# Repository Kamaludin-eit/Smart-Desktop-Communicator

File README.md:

### Smart Desktop Communicator – Design-Dokumentation

**Rev 1.0 | Kamaludin Ali**

\---

#### Übersicht

ESP32-S3-basiertes stationäres IP-Telefon mit PoE-Versorgung, Wired Ethernet,
I2S-Audio und OLED-Display. 4-lagige PCB (150 × 80 mm).

\---

#### Wichtigste Design-Entscheidungen

##### 1\. Mikrocontroller – ESP32-S3-WROOM-1

* Dual-Core LX7, 16 MB Flash, 8 MB PSRAM, 2.4 GHz WLAN integriert
* Natives USB Serial/JTAG auf GPIO19/20 – kein separater USB-UART-Chip nötig
* I2S-Peripheral für DAC (MAX98357A) und PDM-Mikrofon (IM69D120) separat nutzbar
* SPI-Peripheral für W5500 Ethernet-Controller

##### 2\. PoE-Versorgung – TPS2378DDA + PDQE30-Q48-S5-D

* TPS2378DDA: IEEE 802.3at Type-2 PD-Controller (bis 30 W)
* Kein integrierter DC/DC – externer isolierter Wandler PDQE30 (48 V → 5 V, 30 W)
* Isolation trennt PWR\_GND (48 V-Seite) vollständig von GNDD/GNDA (Systemseite)
* Alternativversorgung via USB-C (5 V) mit Schottky-Dioden-OR-Schaltung#

##### 3\. RJ45-Connector – ARJP11A-MASA-B-A-EMU2 (Abracon)

* Integrierte Magnetics, Center-Tap, eingebauter Brückengleichrichter
* PRW+ (Pin 9) / PRW− (Pin 10): rektifizierte PoE-Spannung direkt abgreifbar
* Kein externer Brückengleichrichter oder separates Magnetics-Modul nötig
* Integrierte Status-LEDs (Link/Activity)

##### 4\. Ethernet – W5500

* Hardware-TCP/IP-Stack – entlastet ESP32-S3 vollständig
* SPI-Interface (bis 80 MHz), geringer Softwareaufwand

##### 5\. Audio-Ausgabe – MAX98357A

* I2S DAC + Class-D 3 W Verstärker in einem IC
* BTL-Ausgang: keine DC-Koppelkondensatoren am Lautsprecher nötig
* PVDD über Ferritperle L3 (600 Ω @ 100 MHz, 1 A) von 5V-Rail entkoppelt
* 3.3V-Logiksignale vom ESP32 kompatibel (VIH\_min = 1.5 V)
* Lautsprecher extern im Gehäuse montiert (akustische Echo-Minimierung)

##### 6\. Audio-Eingang – IM69D120 (Infineon)

* MEMS-Mikrofon mit PDM-Ausgang, SNR 69 dB, AOP 120 dB SPL
* Nativ vom ESP32-S3 PDM-Peripheral unterstützt
* VDD über eigene Ferritperle L4 (600 Ω @ 100 MHz, 50 mA) von VCCA\_MIC
* Software-AEC (Acoustic Echo Cancellation) via ESP-ADF

##### 7\. Massekonzept – 2 getrennte GND-Domänen

|Domäne|Verbindung|Komponenten|
|-|-|-|
|GNDD|Solder Jumper Pin 2 |ESP32, W5500 digital, Tasten, LEDs|
|GNDA|Solder Jumper Pin 1|W5500 PHY, IM69D120, MAX98357A, Quarz|

##### 8\. 4-Lagen PCB-Aufbau (150 × 80 mm)

|Lage|Inhalt|
|-|-|
|Layer 1 (Top)|Bauteile + Signale + GNDA-Kupferfläche|
|Layer 2 (In1)|+3,3V  |
|Layer 3 (In2)|GNDD-Kupferfläche|
|Layer 4 (Bottom)|Signale + GNDA-Kupferfläche|

* Digitale GND-Pads auf Top-Layer über Vias mit GNDD (In1) verbunden
* Analoge Komponenten direkt auf GNDA-Fläche (Top-Layer)

##### 9\. Versorgungsschienen

|Schiene|Quelle|Verbraucher|
|-|-|-|
|+48V\_POE|PRW+ via SMAJ58A|TPS2378DDA VDD|
|+5V|PDQE30 Ausgang|MAX98357A, AMS1117|
|+3.3V (VCCD)|AMS1117-3.3|ESP32, W5500 digital, Tasten, LEDs|
|VCCA\_ETH|VCCD via FB\_ETH (600Ω)|W5500 VCCA|
|VCCA\_MIC|VCCD via FB\_MIC (600Ω)|IM69D120 VDD|

### 

##### 10\. ESD-Schutz

|Interface|Schutz|
|-|-|
|PoE 48V|SMAJ58A (unidirektional, 58V)|
|USB-C VBUS|SMAJ5.0A (unidirektional, 5V)|
|USB-C D+/D−|USBLC6-2P6 (Low-C, bidirektional)|
|Ethernet TX/RX|Magnetics-Isolation im ARJP11A|

### 

##### 11\. USB-C – Amphenol 12401610E4#2A

* CC1/CC2: je 5.1 kΩ nach GNDD (5V UFP-Erkennung, kein PD-Controller nötig)
* Schottky-Diode OR-ing mit PoE-Versorgung
* D+/D−: direkt an ESP32 GPIO19/GPIO20 (natives USB JTAG/Serial)

##### 12\. HMI

* SSD1306 OLED 0.96" (128×64, I2C): Anrufstatus, IP, Uhrzeit
* 5 Taster: Annehmen/Auflegen, Vol+, Vol−, Stummschalten, Notruf
* 1 Status-LEDs:  Power(rot)
* Hardware-Entprellung: RC-Glied (100 kΩ + 1 µF) pro Taster

\---

#### Geplante Firmware-Architektur

* **ESP-IDF** v5.x + **ESP-ADF** (Audio Development Framework)
* SIP-Stack: sikorapatryk/sip-call oder OLIMEX/sip\_phone\_example als Referenz
* Codec: G.711 µ-law (PCMU, Payload Type 0)
* AEC: ESP-ADF eingebaut
* W5500-Treiber: arduino-ethernet oder esp-idf-w5500

\---

#### Wählscheibe

Nicht vorgesehen – Anrufsteuerung erfolgt über SIP-Server/PBX-Integration (z.B. FreePBX, Asterisk).

\---

## Revision History

|Rev|Datum|Änderung|
|-|-|-|
|1.0|2026-05|Erstversion|

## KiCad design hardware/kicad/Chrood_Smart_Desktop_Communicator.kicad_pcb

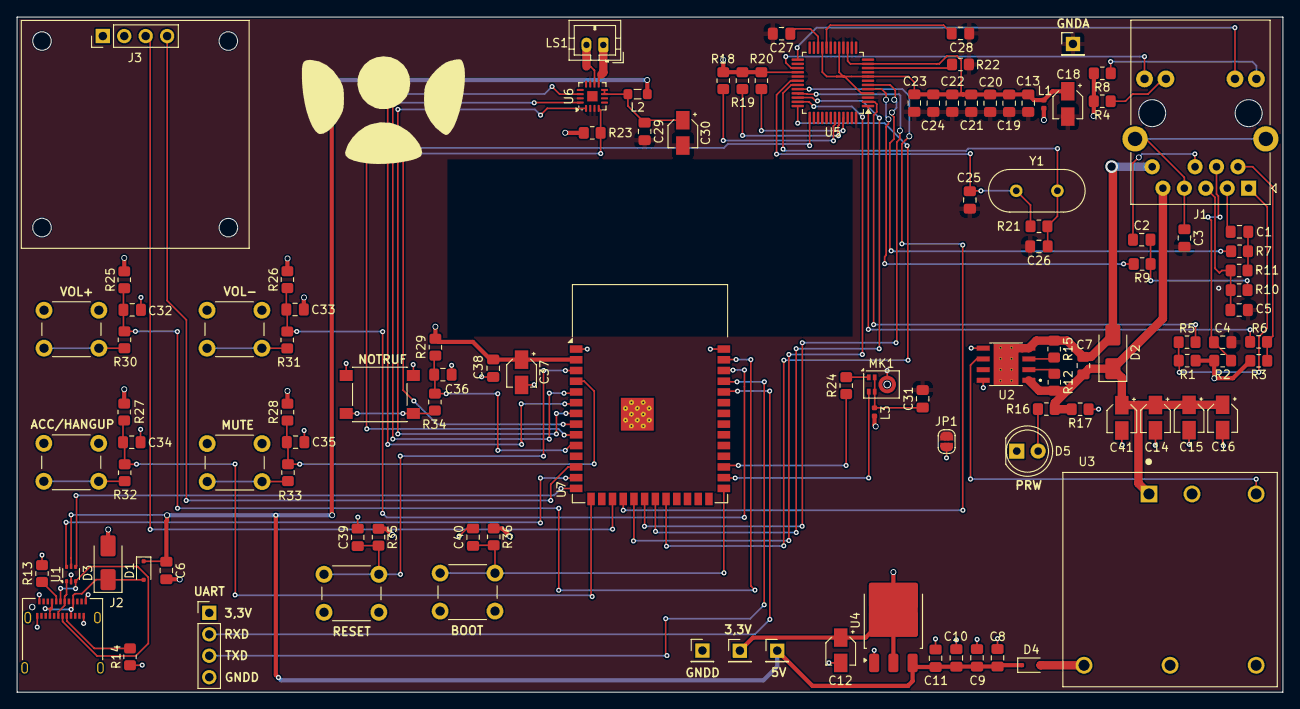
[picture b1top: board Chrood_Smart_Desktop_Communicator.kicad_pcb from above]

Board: 4 copper layers, 150.0 x 80.0 mm, 110 parts (0 on the bottom side), 77 nets.

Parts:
C1, C2: 6,8nF; C_0805_2012Metric_Pad1.18x1.45mm_HandSolder
C3: 1nF; C_0805_2012Metric_Pad1.18x1.45mm_HandSolder
C4: 22nF; C_0805_2012Metric_Pad1.18x1.45mm_HandSolder
C5: 10nF; C_0805_2012Metric_Pad1.18x1.45mm_HandSolder
C6: 100nF; C_0805_2012Metric_Pad1.18x1.45mm_HandSolder
C7, C8, C9, C10, C29, C31: 100n; C_0805_2012Metric_Pad1.18x1.45mm_HandSolder
C11, C13, C19, C20, C21, C22, C23, C24, C38, C39, C40: 0,1u; C_0805_2012Metric_Pad1.18x1.45mm_HandSolder
C12: 47u; CP_Elec_3x5.3
C14, C15, C16, C41: 22u; CP_Elec_3x5.3
C18, C30, C37: 10u; CP_Elec_3x5.3
C25, C26: 18p; C_0805_2012Metric_Pad1.18x1.45mm_HandSolder
C27: 10n; C_0805_2012Metric_Pad1.18x1.45mm_HandSolder
C28: 4,7u; C_0805_2012Metric_Pad1.18x1.45mm_HandSolder
C32, C33, C34, C35, C36: 2,2u; C_0805_2012Metric_Pad1.18x1.45mm_HandSolder
D1, D4: BAT54J; D_SOD-323F
D2: SMAJ58A; D_SMA
D3: SMAJ5.0A; D_SMA
D5: LED; LED_D5.0mm
J1: RJ45_Abracon_ARJP11A-MASA-B-A-EMU2; RJ45_Abracon_ARJP11A-MA_Horizontal
J2: USB_C_Receptacle_USB2.0_14P; USB_C_Receptacle_Amphenol_12401610E4-2A
J3, J4: Conn_01x04_Pin; PinHeader_1x04_P2.54mm_Vertical
JP1: SolderJumper_2_Open; SolderJumper-2_P1.3mm_Open_RoundedPad1.0x1.5mm
L1, L3: 600Ohm@100MHz; L_0402_1005Metric
L2: 600Ohm@100MHz; L_0805_2012Metric_Pad1.05x1.20mm_HandSolder
LS1: Speaker; JST_PH_B2B-PH-K_1x02_P2.00mm_Vertical
MK1: IM69D120; Infineon_PG-LLGA-5-1
R1, R2, R3: 10; R_0805_2012Metric_Pad1.20x1.40mm_HandSolder
R4, R8, R25, R26, R27, R28, R29: 1k; R_0805_2012Metric_Pad1.20x1.40mm_HandSolder
R5, R6, R7, R9, R10, R11: 33; R_0805_2012Metric_Pad1.20x1.40mm_HandSolder
R12: 24k9; R_0805_2012Metric_Pad1.20x1.40mm_HandSolder
R13, R14: 5,1k; R_0805_2012Metric_Pad1.20x1.40mm_HandSolder
R15: 63R4; R_0805_2012Metric_Pad1.20x1.40mm_HandSolder
R16: 32k4; R_0805_2012Metric_Pad1.20x1.40mm_HandSolder
R17: 15k; R_0805_2012Metric_Pad1.20x1.40mm_HandSolder
R18, R19, R20, R35, R36: 10k; R_0805_2012Metric_Pad1.20x1.40mm_HandSolder
R21: 1M; R_0805_2012Metric_Pad1.20x1.40mm_HandSolder
R22: 12k; R_0805_2012Metric_Pad1.20x1.40mm_HandSolder
R23: 100k; R_0805_2012Metric_Pad1.20x1.40mm_HandSolder
R24: 100; R_0805_2012Metric_Pad1.20x1.40mm_HandSolder
R30, R31, R32, R33, R34: 4,7k; R_0805_2012Metric_Pad1.20x1.40mm_HandSolder
SW1: Vol+; SW_PUSH_6mm
SW2: Vol-; SW_PUSH_6mm
SW3: Accept/Hang up; SW_PUSH_6mm
SW4: Mute; SW_PUSH_6mm
SW5: Notruf; SW_SPST_PTS645
SW6, SW7: SW_Push; SW_PUSH_6mm
TP1, TP2, TP3, TP4: TestPoint; PinHeader_1x01_P2.54mm_Vertical
U1: USBLC6-2P6; SOT-666
U2: TPS2378DDA; VREG_LM5017MR_NOPB
U3: PDQ30-Q48-S5-D; CONV_PDQ30-Q48-S5-D
U4: AMS1117CD-3.3; TO-252-3_TabPin2
U5: W5500; LQFP-48_7x7mm_P0.5mm
U6: MAX98357A; TQFN-16-1EP_3x3mm_P0.5mm_EP1.23x1.23mm
U7: ESP32-S3-WROOM-1
Y1: 25MHz; Crystal_HC49-4H_Vertical

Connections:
3,3V: C12.1, C37.1, C38.1, J3.2, J4.1, L1.1, L3.1, R1.2, R2.2, R3.2, R4.2, R8.2, R18.1, R19.1, R20.1, R23.1, R25.2, R26.2, R27.2, R28.2, R29.2, R35.1, R36.1, TP2.1, U4.2 (VO), U5.28 (VDD), U7.2 (3V3)
5V: C6.1, C8.1, C9.1, C10.1, C11.1, D1.1 (K), D4.1 (K), L2.1, TP1.1, U1.5 (VBUS), U4.3 (VI)
/Microcontroller/BOOT: C40.1, R36.2, SW7.1, U7.27 (IO0)
/Microcontroller/CHIP_PU: C39.1, R35.2, SW6.1, U7.3 (EN)
/Microcontroller/RXD: J4.2, U7.36 (RXD0)
/Microcontroller/TXD: J4.3, U7.37 (TXD0)
/Power_Supply/PRW+: C7.1, C14.1, C15.1, C16.1, C41.1, D2.1 (A1), J1.9 (V+), R12.2, R16.2, R17.2, U2.1 (VDD), U3.1 (+VIN)
/Power_Supply/PRW-: C7.2, D2.2 (A2), J1.10 (V-), R15.1, U2.4 (VSS), U2.9 (PAD)
/Power_Supply/PoE_ACTIVE: U2.6 (CDB), U3.6 (REMOTE)
ACT_LED: J1.14, U5.27 (ACTLED)
ESP_ETH_CS: U5.32 (~SCS), U7.18 (IO10)
ESP_ETH_INT: U5.36 (~INT), U7.22 (IO14)
ESP_ETH_MISO: U5.34 (MISO), U7.21 (IO13)
ESP_ETH_MOSI: U5.35 (MOSI), U7.19 (IO11)
ESP_ETH_RST: U5.37 (~RST), U7.8 (IO15)
ESP_ETH_SCLK: U5.33 (SCLK), U7.20 (IO12)
ESP_MIC_CLK: MK1.3 (CLOCK), U7.28 (IO35)
ESP_MIC_DATA: R24.2, U7.29 (IO36)
ESP_OLED_SCL: J3.3, U7.17 (IO9)
ESP_OLED_SDA: J3.4, U7.12 (IO8)
ESP_SPKR_BCLK: U6.16 (BCLK), U7.5 (IO5)
ESP_SPKR_DIN: U6.1 (DIN), U7.7 (IO7)
ESP_SPKR_LRCLK: U6.14 (LRCLK), U7.6 (IO6)
ESP_SPKR_SD: R23.2, U6.4 (~SD_MODE), U7.9 (IO16)
ESP_SW_ACC/HANGUP: C34.1, R27.1, R32.2, U7.15 (IO3)
ESP_SW_MUTE: C35.1, R28.1, R33.2, U7.4 (IO4)
ESP_SW_NOTRUF: C36.1, R29.1, R34.2, U7.10 (IO17)
ESP_SW_VOL+: C32.1, R25.1, R30.2, U7.39 (IO1)
ESP_SW_VOL-: C33.1, R26.1, R31.2, U7.38 (IO2)
ESP_USB_D+: U1.4 (I/O2), U7.14 (IO20)
ESP_USB_D-: U1.6 (I/O1), U7.13 (IO19)
GNDA: C3.2, C4.2, C5.2, C13.2, C18.2, C19.2, C20.2, C21.2, C22.2, C23.2, C24.2, C25.2, C26.2, C27.2, C28.2, C29.2, C30.2, C31.2, JP1.1 (A), MK1.5 (GND), R22.2, TP3.1, U5.3 (AGND), U5.9 (AGND), U5.14 (AGND), U5.16 (AGND), U5.19 (AGND), U5.29 (GND), U5.48 (AGND), U6.2 (GAIN_SLOT), U6.3 (GND), U6.11 (GND), U6.15 (GND)
GNDD: C6.2, C8.2, C9.2, C10.2, C11.2, C12.2, C14.2, C15.2, C16.2, C32.2, C33.2, C34.2, C35.2, C36.2, C37.2, C38.2, C39.2, C40.2, C41.2, D3.2 (A2), D5.1 (K), J2.A1 (GND), J2.A12 (GND), J2.B1 (GND), J2.B12 (GND), J2.S1 (SHIELD), J3.1, J4.4, JP1.2 (B), R13.1, R14.1, R17.1, SW1.1, SW2.1, SW3.1, SW4.1, SW5.1, SW6.2, SW7.2, TP4.1, U1.2 (GND), U2.5 (RTN), U2.8 (APD), U3.2 (-VIN), U3.5 (-VOUT), U4.1 (GND), U7.1 (GND), U7.40 (GND), U7.41 (GND)
LINK_LED: J1.12, U5.25 (LINKLED)
unnamed: C1.2, R7.1, R11.2
unnamed: C2.2, R9.1, R10.2
unnamed: C3.1, J1.7, J1.SH
unnamed: C29.1, C30.1, L2.2, U6.7 (VDD), U6.8 (VDD)
unnamed: D1.2 (A), D3.1 (A1), J2.A4 (VBUS), J2.A9 (VBUS), J2.B4 (VBUS), J2.B9 (VBUS)
unnamed: D4.2 (A), U3.3 (+VOUT)
unnamed: D5.2 (A), R16.1
unnamed: J1.11, R8.1
unnamed: J1.13, R4.1
unnamed: C5.1, J1.5 (RCT), R10.1, R11.1
unnamed: C1.1, J1.3 (RD+)
unnamed: C2.1, J1.6 (RD-)
unnamed: C4.1, J1.4 (TCT), R2.1
unnamed: J1.1 (TD+), R1.1, R5.1
unnamed: J1.2 (TD-), R3.1, R6.1
unnamed: J2.A5 (CC1), R13.2
unnamed: J2.B5 (CC2), R14.2
unnamed: J2.A6 (D+), J2.B6 (D+), U1.3 (I/O2)
unnamed: J2.A7 (D-), J2.B7 (D-), U1.1 (I/O1)
unnamed: MK1.1 (DATA), R24.1
unnamed: C31.1, L3.2, MK1.2 (VDD), MK1.4 (SELECT)
unnamed: R30.1, SW1.2
unnamed: R31.1, SW2.2
unnamed: R32.1, SW3.2
unnamed: R33.1, SW4.2
unnamed: R34.1, SW5.2
unnamed: R15.2, U2.3 (CLS)
unnamed: R12.1, U2.2 (DEN)
unnamed: C27.1, U5.22 (1V2O)
unnamed: R22.1, U5.10 (EXRES1)
unnamed: R20.2, U5.45 (PMODE0)
unnamed: R19.2, U5.44 (PMODE1)
unnamed: R18.2, U5.43 (PMODE2)
unnamed: C28.1, U5.20 (TOCAP)
unnamed: C25.1, R21.1, U5.30 (XI/CLKIN), Y1.1
unnamed: C26.1, R21.2, U5.31 (XO), Y1.2
unnamed: LS1.2, U6.10 (OUTN)
unnamed: LS1.1, U6.9 (OUTP)
RXN: R9.2, U5.5 (RXN)
RXP: R7.2, U5.6 (RXP)
TXN: R6.2, U5.1 (TXN)
TXP: R5.2, U5.2 (TXP)
VCCA: C13.1, C18.1, C19.1, C20.1, C21.1, C22.1, C23.1, C24.1, L1.2, U5.4 (AVDD), U5.8 (AVDD), U5.11 (AVDD), U5.15 (AVDD), U5.17 (AVDD), U5.21 (AVDD)

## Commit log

2026-06-08 "Add folder structure"
2026-06-08 Add files via upload
    Hardware: Add KiCad project files
2026-06-08 Add files via upload
    Hardware: Add schematic PDFs all 5 sheets
2026-06-08 Add files via upload
    Hardware: Add Bill of Materials Rev 1.0
2026-06-08 Add files via upload
    Docs: Add PCB layout preview
